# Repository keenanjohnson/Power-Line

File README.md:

###Current design###
4 "devices", communication is from top to bottom and vice versa:

* Arduino + Ethernet Shield -> (Ethernet cable) -> Router
* Router -> (Ethernet cable) -> PLN 1
* PLN 1 -> power line -> PLN 2
* PLN 2 -> (Ethernet cable) -> Arduino + Ethernet Sheild

####Information####
Ensure that the node devices all have different MAC addresses to get different IP addresses from the host router. The router should be set up to deliver a certain IP address to the MAC address of the base station. In our project's current state, it is meant to be delivered 192.168.2.50 but will setup its own IP address if that one is unobtainable. The nodes will just listen for the IP address so this is mainly important for access the website, which you will require you to know the IP address.

###Powerline###

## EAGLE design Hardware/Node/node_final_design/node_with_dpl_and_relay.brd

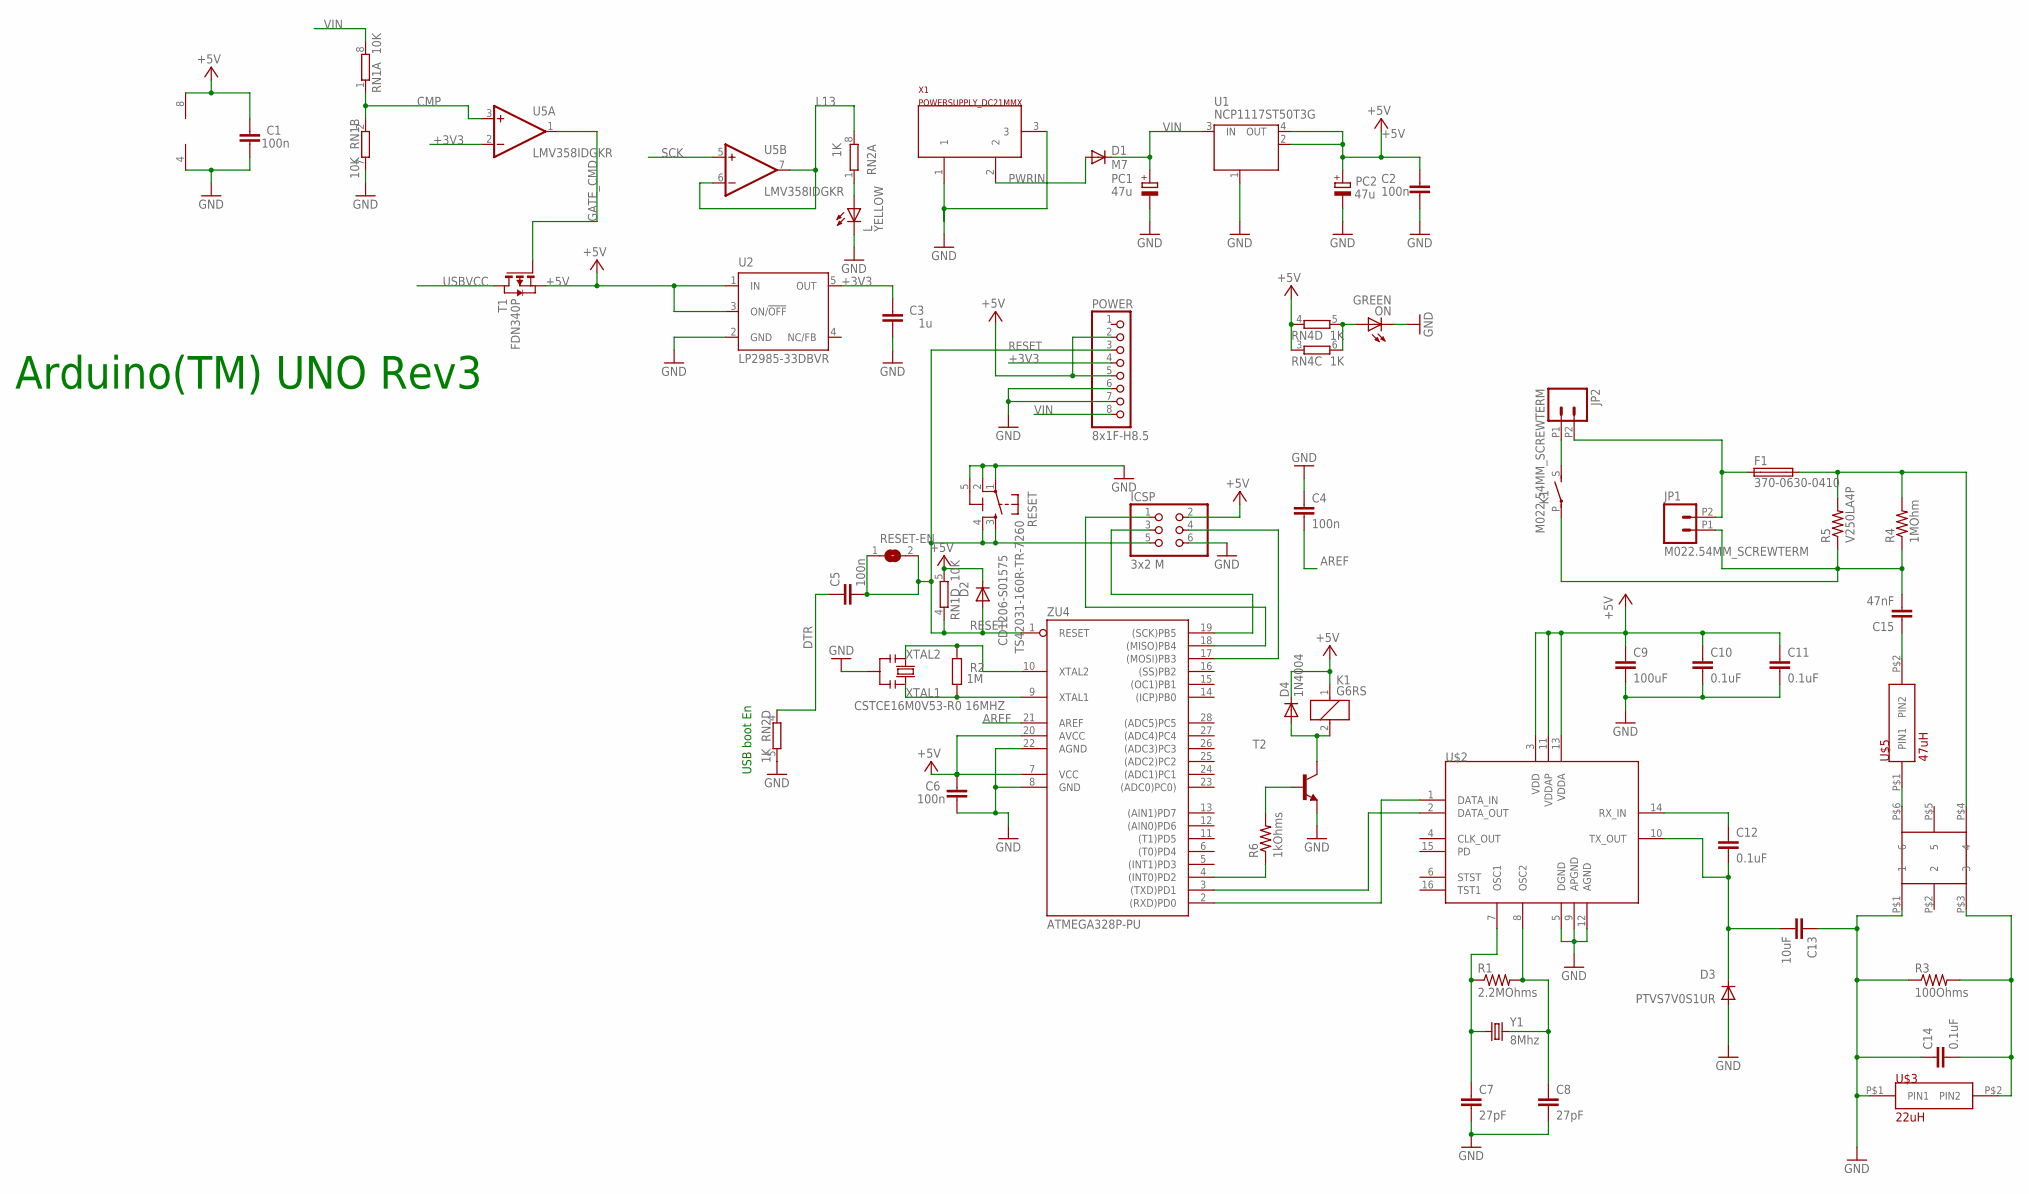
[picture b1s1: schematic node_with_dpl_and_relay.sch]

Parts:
C1, C2, C4, C5, C6: 100n; C0603-ROUND
C3: 1u; C0603-ROUND
C7, C8: 27pF; 1206
C9: 100uF; 1206
C10, C11, C14: 0.1uF; 1206
C12: 0.1uF; AXIAL-5MM
C13: 10uF; CAP-PTH-SMALL
C15: 47nF; C15B5
D1: M7; SMB
D2: CD1206-S01575; MINIMELF
D3: PTVS7V0S1UR; SOD-123_MINI-SMA
D4: 1N4004; DO41-10
F1: 370-0630-0410; TR5
ICSP: 3x2 M; 2X03
JP1, JP2: M022.54MM_SCREWTERM; 1X02_2.54_SCREWTERM
K1: G6RS
L: YELLOW; CHIP-LED0805
ON: GREEN; CHIP-LED0805
PC1, PC2: 47u; PANASONIC_D
POWER: 8x1F-H8.5; 1X08
R1: 2.2MOhms; 1206
R2: 1M; R0603-ROUND
R3: 100Ohms; AXIAL-0.5
R4: 1MOhm; AXIAL-0.3-KIT
R5: V250LA4P; AXIAL-0.4
R6: 1kOhms; 0204V
RESET: TS42031-160R-TR-7260; TS42
RESET-EN: SJ
RN1: 10K; CAY16
RN2, RN4: 1K; CAY16
T1: FDN340P; SOT-23
T2: 2N5401-NPN-TO92-CBE; TO92-CBE
U1: NCP1117ST50T3G; SOT223
U2: LP2985-33DBVR; SOT23-DBV
U5: LMV358IDGKR; MSOP08
U$2: TDA5052AT; SO16L
U$3: 22uH; RFB0807-220L
U$4: 78250MC
U$5: 47uH; RFB0807-220L
X1: POWERSUPPLY_DC21MMX; POWERSUPPLY_DC-21MM
Y1: 8Mhz; HC49US
Y2: CSTCE16M0V53-R0 16MHZ; RESONATOR
ZU4: ATMEGA328P-PU; DIL28-3

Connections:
+3V3: C3.2, POWER.4, U2.5 (OUT), U5.2 (-IN)
+5V: C1.2, C2.2, C6.2, C9.1, C10.1, C11.1, D2.C, D4.C, ICSP.2, K1.1, PC2.+, POWER.2, POWER.5, RN1.5 (2), RN4.3 (1), RN4.4 (1), T1.2 (S), U1.2 (OUT), U1.4 (OUT), U2.1 (IN), U2.3 (ON/!OFF), U5.8 (V+), U$2.3 (VDD), U$2.11 (VDDAP), U$2.13 (VDDA), ZU4.7 (VCC), ZU4.20 (AVCC)
AREF: C4.2, ZU4.21 (AREF)
CMP: RN1.1, RN1.2 (1), U5.3 (+IN)
DTR: C5.1, RN2.4 (1)
GATE_CMD: T1.3 (G), U5.1 (OUT)
GND: C1.1, C2.1, C3.1, C4.1, C6.1, C7.2, C8.2, C9.2, C10.2, C11.2, C13.1, C14.1, D3.A, ICSP.6, L.C, ON.C, PC1.-, PC2.-, POWER.6, POWER.7, R3.P$1 (1), RESET.1, RESET.2, RESET.5 (5-GND), RN1.7 (2), RN2.5 (2), T2.E, U1.1 (GND/ADJ), U2.2 (GND), U5.4 (V-), U$2.5 (DGND), U$2.9 (APGND), U$2.12 (AGND), U$3.P$1 (PIN1), U$4.P$1 (1), X1.1, X1.3, Y2.2, ZU4.8 (GND), ZU4.22 (AGND)
L13: RN2.8 (2), U5.6 (-IN), U5.7 (OUT)
MISO: ICSP.1, ZU4.18 ((MISO)PB4)
MOSI: ICSP.4, ZU4.17 ((MOSI)PB3)
unnamed: L.A, RN2.1
unnamed: C8.1, R1.2, U$2.8 (OSC2), Y1.2
unnamed: ON.A, RN4.5 (2), RN4.6 (2)
unnamed: C7.1, R1.1, U$2.7 (OSC1), Y1.1
unnamed: C12.P$1 (1), U$2.14 (RX_IN)
unnamed: C12.P$2 (2), C13.2, D3.C, U$2.10 (TX_OUT)
unnamed: C14.2, R3.P$2 (2), U$3.P$2 (PIN2), U$4.P$3 (3)
unnamed: U$4.P$6 (6), U$5.P$1 (PIN1)
unnamed: C15.1, U$5.P$2 (PIN2)
unnamed: F1.2, R4.P$2 (2), R5.P$2 (2), U$4.P$4 (4)
unnamed: JP2.P1 (1), K1.S
unnamed: F1.1, JP1.P2 (2), JP2.P2 (2)
unnamed: U$2.2 (DATA_OUT), ZU4.3 ((TXD)PD1)
unnamed: U$2.1 (DATA_IN), ZU4.2 ((RXD)PD0)
unnamed: R6.1, ZU4.4 ((INT0)PD2)
unnamed: R6.2, T2.B
unnamed: D4.A, K1.2, T2.C
unnamed: C15.2, JP1.P1 (1), K1.P, R4.P$1 (1), R5.P$1 (1)
PWRIN: D1.A, X1.2
RESET: C5.2, D2.A, ICSP.5, POWER.3, RESET.3, RESET.4, RESET-EN.1, RESET-EN.2, RN1.4 (1), ZU4.1 (RESET)
SCK: ICSP.3, U5.5 (+IN), ZU4.19 ((SCK)PB5)
USBVCC: T1.1 (D)
VIN: D1.C, PC1.+, POWER.8, RN1.8 (2), U1.3 (IN)
XTAL1: R2.1, Y2.3, ZU4.9 (XTAL1)
XTAL2: R2.2, Y2.1, ZU4.10 (XTAL2)

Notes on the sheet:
Arduino(TM) UNO Rev3
USB boot En

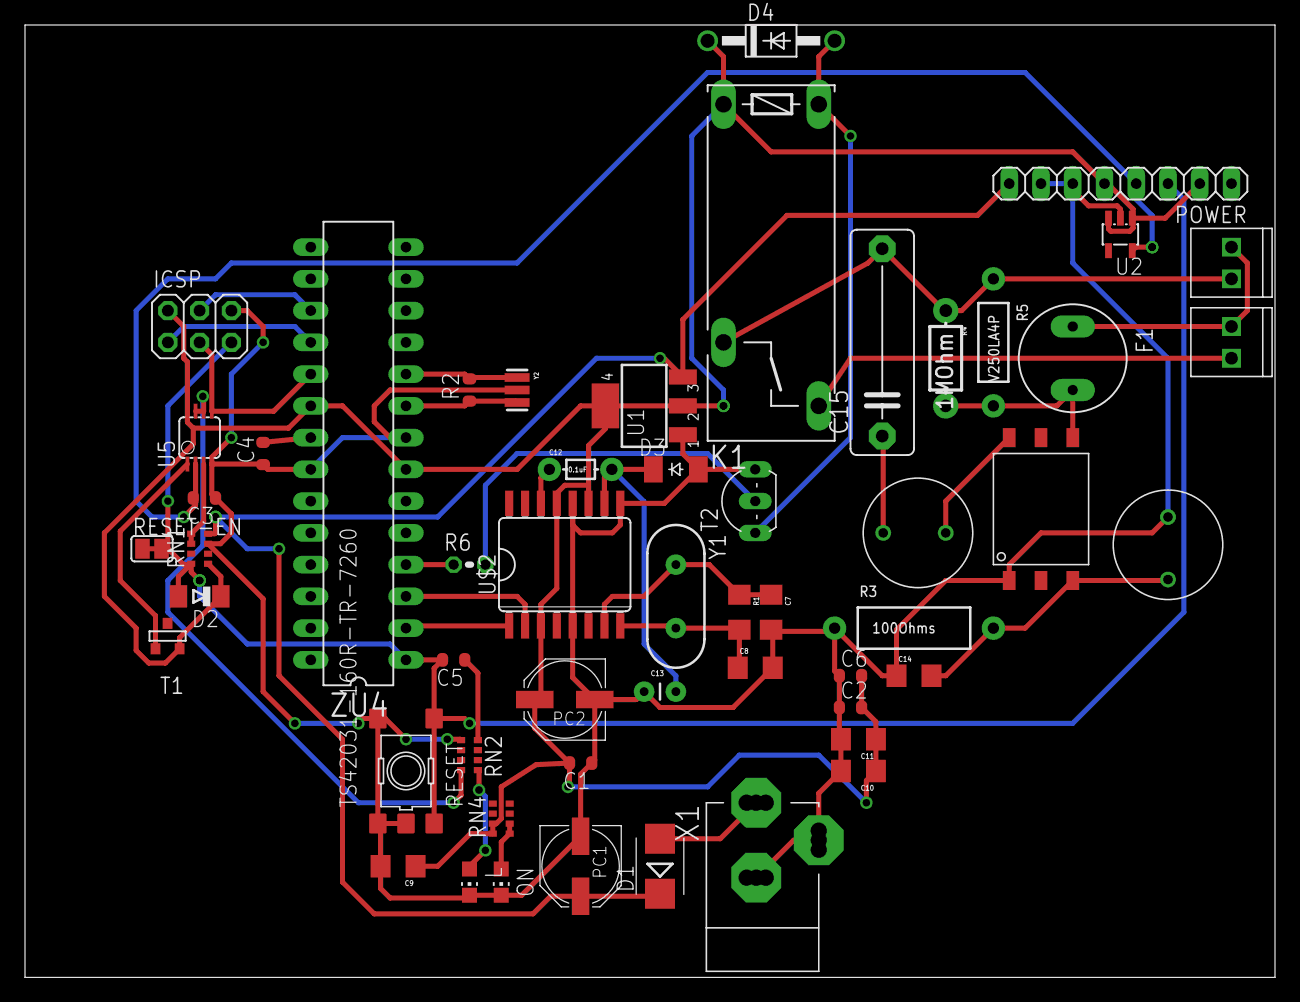
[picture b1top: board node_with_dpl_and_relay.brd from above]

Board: 2 copper layers, 100.0 x 76.2 mm, 53 parts (0 on the bottom side), 34 nets.

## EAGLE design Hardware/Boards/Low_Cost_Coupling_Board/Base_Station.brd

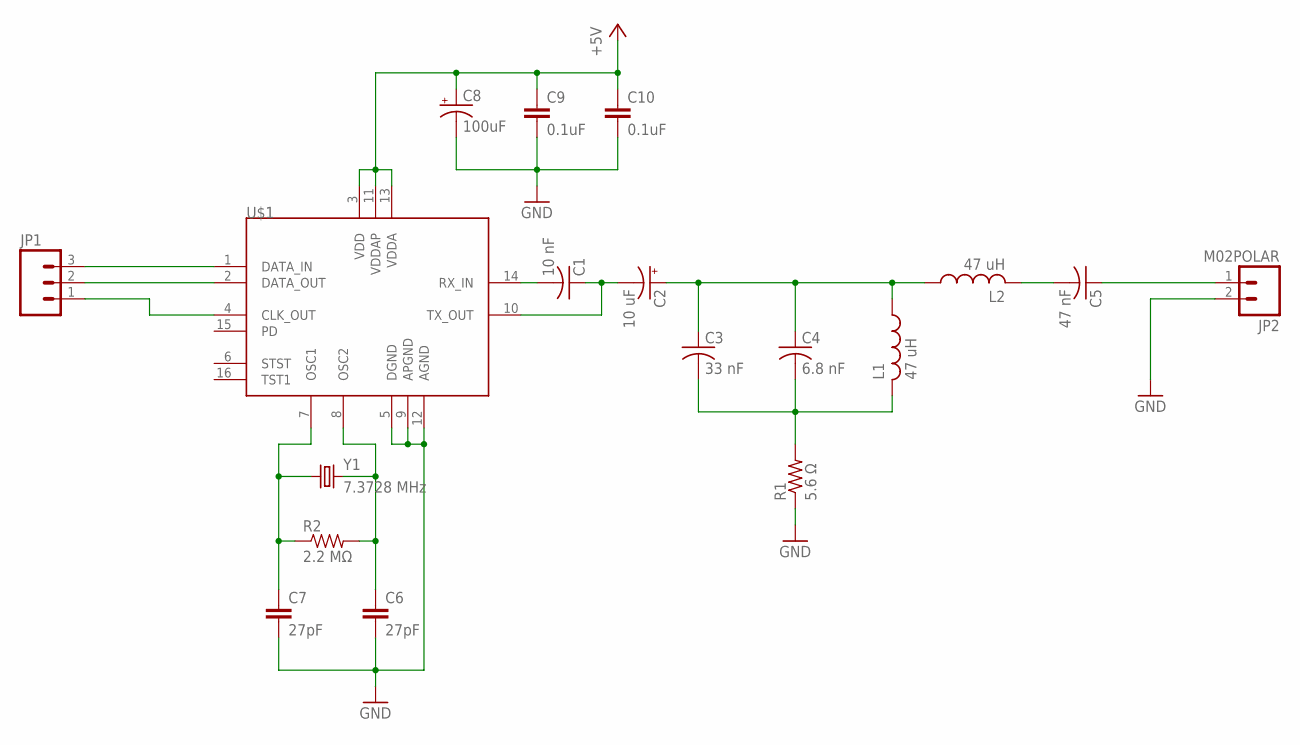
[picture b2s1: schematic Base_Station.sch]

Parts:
C1: 10 nF; C025-030X050
C2: 10 uF; E2-5
C3: 33 nF; C050-050X075
C4: 6.8 nF; C102-043X133
C5: 47 nF; C075-063X106
C6, C7: 27pF; CAP-PTH-5MM
C8: 100uF; CPOL-RADIAL-100UF-25V
C9, C10: 0.1uF; CAP-PTH-5MM
JP1: M03POLAR; MOLEX-1X3
JP2: M02POLAR; MOLEX-1X2
L1: 47 uH; 0204/7
L2: 47 uH; 0207/10
R1: 5.6 Ω; 0207/7
R2: 2.2 MΩ; AXIAL-0.4
U$1: TDA5052AT; SO16L
Y1: 7.3728 MHz; HC49US

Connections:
+5V: C8.1 (+), C9.1, C10.1, U$1.3 (VDD), U$1.11 (VDDAP), U$1.13 (VDDA)
GND: C6.2, C7.2, C8.2 (-), C9.2, C10.2, JP2.2, R1.1, U$1.5 (DGND), U$1.9 (APGND), U$1.12 (AGND)
unnamed: C1.2, U$1.14 (RX_IN)
unnamed: C5.2, L2.2
unnamed: C1.1, C2.-, U$1.10 (TX_OUT)
unnamed: C2.+, C3.1, C4.1, L1.1, L2.1
unnamed: C3.2, C4.2, L1.2, R1.2
unnamed: C5.1, JP2.1
unnamed: C7.1, R2.P$1 (1), U$1.7 (OSC1), Y1.1
unnamed: C6.1, R2.P$2 (2), U$1.8 (OSC2), Y1.2
unnamed: JP1.3, U$1.1 (DATA_IN)
unnamed: JP1.2, U$1.2 (DATA_OUT)
unnamed: JP1.1, U$1.4 (CLK_OUT)

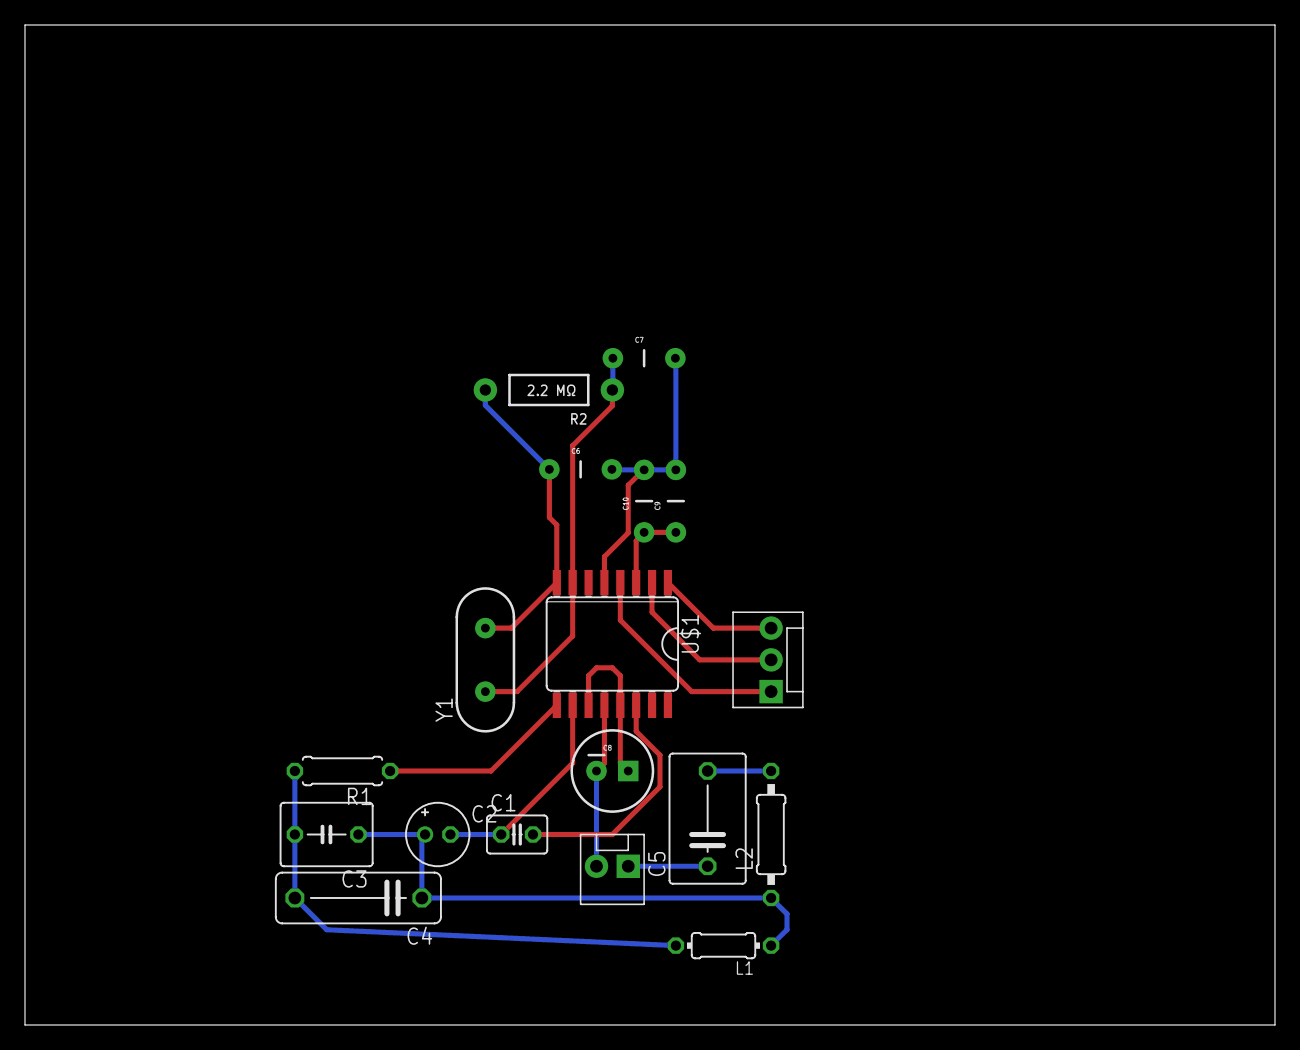
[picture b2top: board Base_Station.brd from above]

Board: 2 copper layers, 100.0 x 80.0 mm, 18 parts (0 on the bottom side), 13 nets.

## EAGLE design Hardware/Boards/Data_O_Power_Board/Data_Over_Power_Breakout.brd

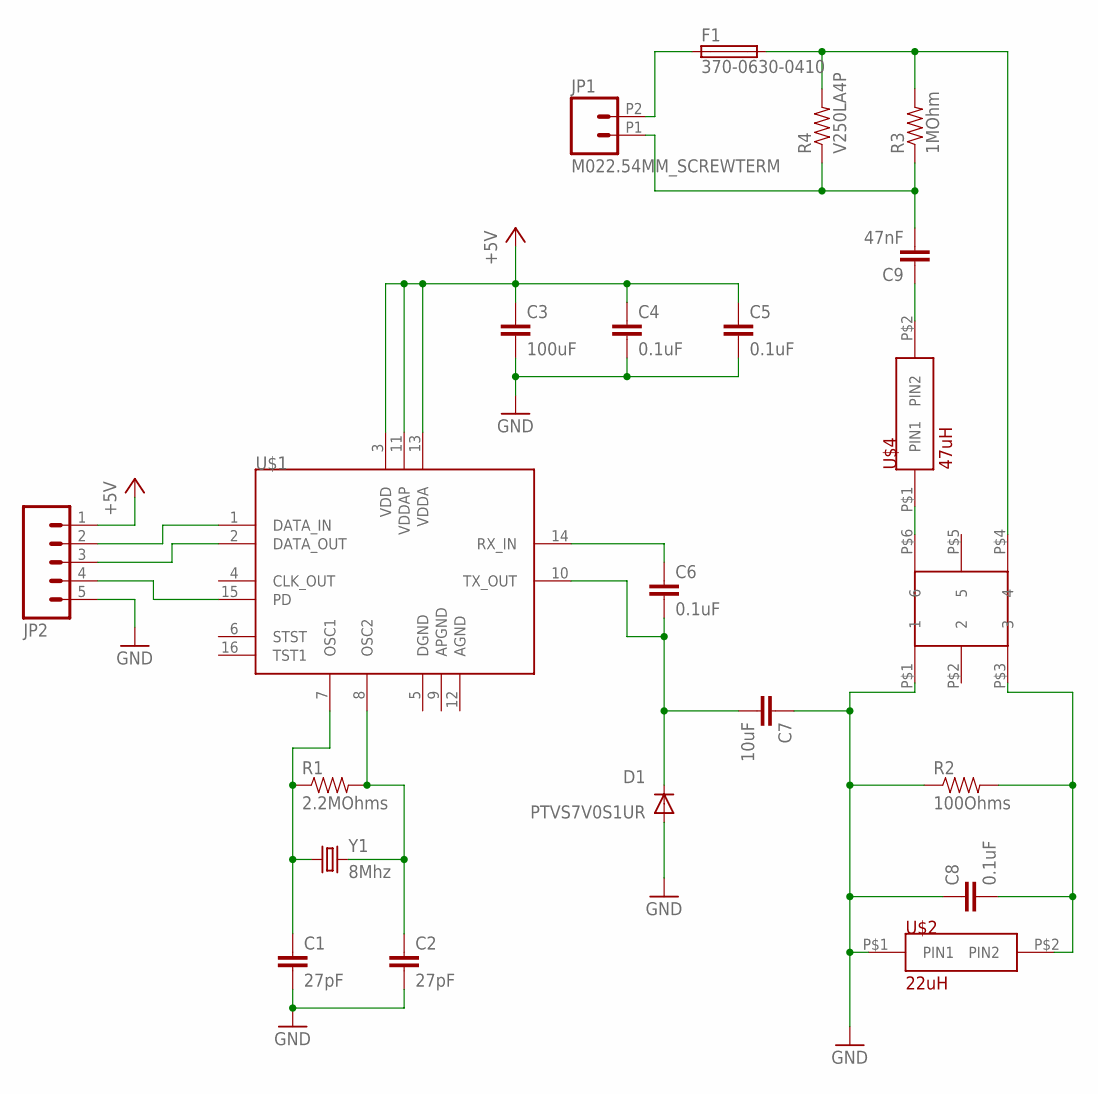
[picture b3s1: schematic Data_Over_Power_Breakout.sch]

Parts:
C1, C2: 27pF; 1206
C3: 100uF; 1206
C4, C5, C8: 0.1uF; 1206
C6: 0.1uF; AXIAL-5MM
C7: 10uF; CAP-PTH-SMALL
C9: 47nF; C15B5
D1: PTVS7V0S1UR; SOD-123_MINI-SMA
F1: 370-0630-0410; TR5
JP1: M022.54MM_SCREWTERM; 1X02_2.54_SCREWTERM
JP2: M05PTH_LONGPADS; 1X05_LONGPADS
R1: 2.2MOhms; 1206
R2: 100Ohms; AXIAL-0.5
R3: 1MOhm; AXIAL-0.3-KIT
R4: V250LA4P; AXIAL-0.4
U$1: TDA5052AT; SO16L
U$2: 22uH; RFB0807-220L
U$3: 78250MC
U$4: 47uH; RFB0807-220L
Y1: 8Mhz; HC49US

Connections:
+5V: C3.1, C4.1, C5.1, JP2.1, U$1.3 (VDD), U$1.11 (VDDAP), U$1.13 (VDDA)
GND: C1.2, C2.2, C3.2, C4.2, C5.2, C7.1, C8.1, D1.A, JP2.5, R2.P$1 (1), U$2.P$1 (PIN1), U$3.P$1 (1)
unnamed: C2.1, R1.2, U$1.8 (OSC2), Y1.2
unnamed: C1.1, R1.1, U$1.7 (OSC1), Y1.1
unnamed: U$3.P$6 (6), U$4.P$1 (PIN1)
unnamed: C8.2, R2.P$2 (2), U$2.P$2 (PIN2), U$3.P$3 (3)
unnamed: C6.P$1 (1), U$1.14 (RX_IN)
unnamed: C6.P$2 (2), C7.2, D1.C, U$1.10 (TX_OUT)
unnamed: C9.1, U$4.P$2 (PIN2)
unnamed: C9.2, JP1.P1 (1), R3.P$1 (1), R4.P$1 (1)
unnamed: F1.2, R3.P$2 (2), R4.P$2 (2), U$3.P$4 (4)
unnamed: F1.1, JP1.P2 (2)
unnamed: JP2.2, U$1.1 (DATA_IN)
unnamed: JP2.3, U$1.2 (DATA_OUT)
unnamed: JP2.4, U$1.15 (PD)

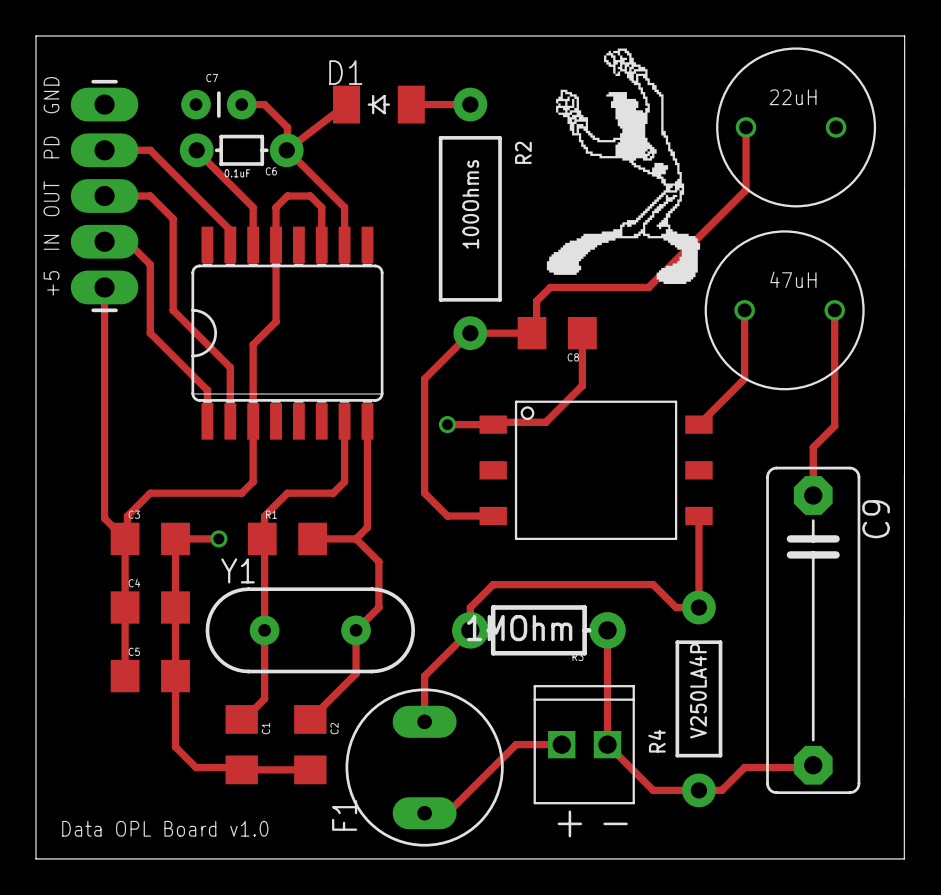
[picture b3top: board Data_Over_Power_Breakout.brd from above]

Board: 2 copper layers, 48.3 x 45.7 mm, 22 parts (0 on the bottom side), 15 nets.

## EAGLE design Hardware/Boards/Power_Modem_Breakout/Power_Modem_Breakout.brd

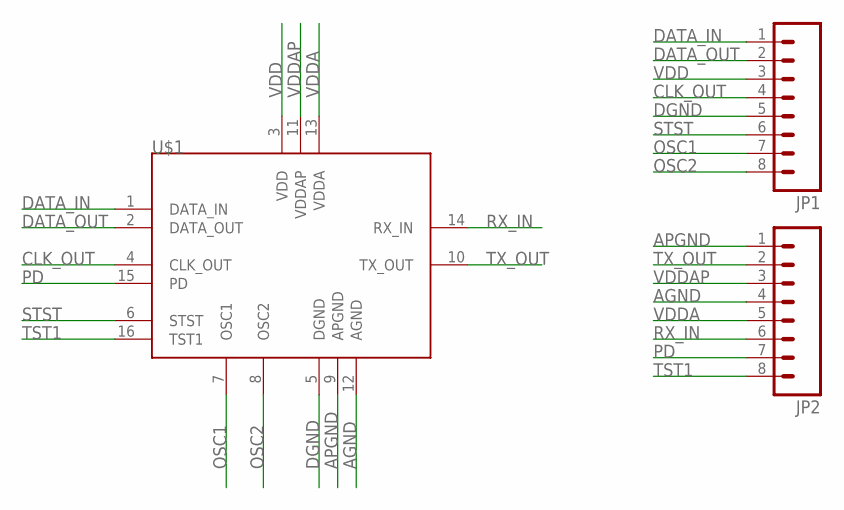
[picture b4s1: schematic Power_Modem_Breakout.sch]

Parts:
JP1, JP2: M08LONGPADS; 1X08_LONGPADS
U$1: TDA5052AT; SO16L

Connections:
AGND: JP2.4, U$1.12 (AGND)
APGND: JP2.1, U$1.9 (APGND)
CLK_OUT: JP1.4, U$1.4 (CLK_OUT)
DATA_IN: JP1.1, U$1.1 (DATA_IN)
DATA_OUT: JP1.2, U$1.2 (DATA_OUT)
DGND: JP1.5, U$1.5 (DGND)
OSC1: JP1.7, U$1.7 (OSC1)
OSC2: JP1.8, U$1.8 (OSC2)
PD: JP2.7, U$1.15 (PD)
RX_IN: JP2.6, U$1.14 (RX_IN)
STST: JP1.6, U$1.6 (STST)
TST1: JP2.8, U$1.16 (TST1)
TX_OUT: JP2.2, U$1.10 (TX_OUT)
VDD: JP1.3, U$1.3 (VDD)
VDDA: JP2.5, U$1.13 (VDDA)
VDDAP: JP2.3, U$1.11 (VDDAP)

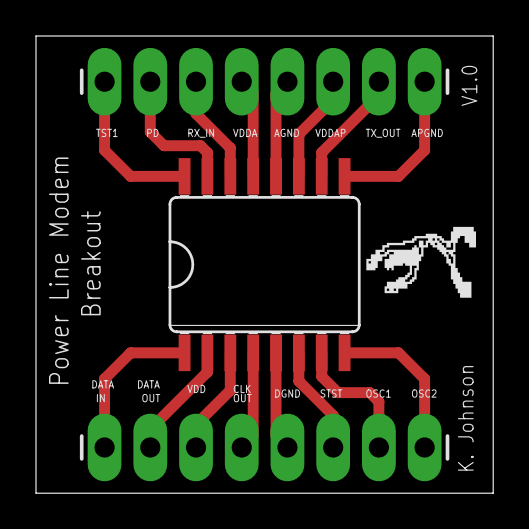
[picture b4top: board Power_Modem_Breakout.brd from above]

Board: 2 copper layers, 25.4 x 25.4 mm, 3 parts (0 on the bottom side), 16 nets.

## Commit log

2014-01-18 Adding power modem datasheet
2014-01-18 Adding Eagle Library for Power Modem
2014-01-18 Created simple breakout for power modem
2014-01-18 Added silkscreen layer
2014-01-18 Adding OSH Park DRC file
2014-01-18 Added really important things to breakout
2014-01-18 Fixed PL so it renders correctly
2014-01-18 Fixed my name
2014-01-18 Removed this file. I don't know why
2014-01-21 Adding image
2014-01-23 Fixed my name layer.
2014-01-29 Adding schematic for power line breakout
2014-01-29 Added DOP Board
2014-02-20 Commiting the test code
2014-02-23 adding application notes
2014-02-23 Updated code from testing
2014-02-24 Add test code to use one Uno + 2 PLN boards
2014-02-25 Working serial between two PLNs
2014-02-25 Update .gitignore to ignore .DS_Store files
2014-02-25 Not sure what changed
2014-03-02 Add webserver code and webpage
    This code will communicate with the webpage via an XML response.
    The status reflected is of the pin 7 and 8 button being emulated
    by a wire connected to GND (off) or 3.3V (on). The code contains
    the first pass at adding elements on the fly commented out.
2014-03-02 Add ability to construct HTML elements in real time
    Constructs the HTML elements representing the lights on the fly
    by appending new elements to the single one on the page based
    upon the XML response.
2014-03-04 Adding webduino stuff
2014-03-04 Introduce packet-level protocol draft
2014-03-18 Update one Uno code to signal LED
2014-03-18 Really dumb code that works
2014-03-24 Adding schematic for long term hardware design
2014-03-25 Added Schematic for low cost coupling board
    Hopefully I didn't mess it up too badly
2014-03-26 Finished schematic for low cost coupling board.
2014-03-27 Adding test code for Matt
2014-03-27 Partially completed low cost coupling board
    Decided it wasn't necessary tonight
2014-04-02 Move WebServer.h to proper folder
2014-04-10 Add initial code for basestation and node
    The Code folder now contains the code for both Arduinos doing
    communication through the powerline. The layout of the components
    is detailed in the header of the files. This should enable
    dynamic connection to the server via grabbing a UDP broadcast
    of the basestation's IP address. The basestation will see the
    client and send commands through the PLN device. The node device
2014-04-10 Move old code to Testing folder and update README
2014-04-10 Fix and update README
2014-04-10 Reset connection to server on disconnect
    If TCP connection to server has gone down, look for UDP broadcast
    and reconnect to new server IP.
    Issue: #10
2014-04-10 Fix send_cmd_to_client function
    Update function to send data to the individual client passed into
    the function instead of to all connected clients.
2014-04-10 Update receiving algorithm on client side
    We can assume the data will be received correctly because of using
    the TCP connection to exchange the data.
2014-04-10 Add dynamic node addition/removal
    client.connected() never seems to disconnect on the server side.
    Use both client.connected() and whether the server can write to
    the client to determine the status of the TCP connection. Server
    will determine that client has been dropped and begin searching
    for a new clients again.
    Issue: #2
2014-04-12 Removing old webduino
2014-04-12 Bring in Webduino submodule
    After this commit you'll need to run 'git submodule update --init'
    to bring in the Webduino submodule.
2014-04-12 Add on/off response to commands
    Initialize relay pin (5) as output and set the value upon receipt of
    the NODE_OFF or NODE_ON commands.
    Issue: #4
2014-04-12 Adding Wedduino file
2014-04-12 Removing old example
2014-04-14 #1 Added basic hello world webduino routing
2014-04-14 Add some uncommitted changes to documentation
2014-04-15 Non working webserver base station with SD card read
2014-04-15 Move strings to progmem
    Move const arrays to progmem to save some RAM space. Remove unused
    globally declared objects. Add start of NODE_STATUS command, still
    need to add implementation.
2014-04-15 Removing old webserver stuff
2014-04-16 Web server is close ish to working
2014-04-16 Hello World with integrated Webduino
2014-04-16 Webduino now serves HTML page from SD card
2014-04-16 Adding index file from Matt's old code as base
2014-04-16 Adding working webserver stuff
2014-04-16 Add status command and server command parsing
    Node can now return status to server. Server can now parse commands
    /respones sent back from node devices.
    Issue: #13
2014-04-16 Add node on/off functionality with status update
    Issue: #6
2014-04-18 Send NODE_STATUS to server after NODE_ON/OFF
    Process NODE_ON/OFF and send NODE_STATUS to server to update its
    state for the selected node.
    Issue: #16
2014-04-18 Add node disconnecting from base logic
    The nodes can now detect that the base has been disconnected and
    they will starting searching for new base. They rely on a cmd
    sent to server (NODE_KEEP_ALIVE) receiving a reply back under the
    time limit (2000 loops). Every NODE_KEEP_ALIVE sent from server
    contains the status of the relay pin, so use this to update the
    node_status on the server side. This will cause less traffic than
2014-04-18 Add server disconnecting from node logic
    Server will disconnect from node if it hasn't seen a NODE_KEEP_ALIVE
    in (2 * LOOP_COUNT_RESET). It will then return to the accepting
    connections state. The current timeout is loop cycle based but
    it would be better to do it time based.
    Issue: #15
2014-04-18 Start multinode support
    Setup arrays for node status/timeout and for individual Ethernet
    Client storage per connected node. Limit connections by max sockets
    available to Ethernet Shield. Most accesses are hard coded due to
    the server only giving out the 0x01 ID to all connected nodes.
    Looping over the arrays needs to be added to finish this setup.
    Issue: #7
2014-04-21 #14 Webpage now dynamically generates buttons for lights. Light state is also represented by button color. Commanding is broken for now
2014-04-21 #14 Device buttons now generate unique post messages
2014-04-22 Change node/server timeout to time based
    Nodes now disconnect from server if a KEEP_ALIVE isn't received
    within 0.5 seconds from sending one. Server now disconnects if a
    KEEP_ALIVE isn't recieved from a node within 1 second.
    Add looping over multiple nodes. This needs to be tested before it
    can be verified.
    Issue: #18
2014-04-22 Complete multi-node processing
    Multiple nodes can now connect. Nodes will timeout individually
    based on the previous timeout values. A new ID will be given to a
    new connection that hasn't been established before. All Serial.
    print/println strings have now been moved to PROGMEM to save RAM.
    IMPORTANT:
    To get this patch to work, you must copy the files in
2014-04-22 Updated webpage post request
2014-04-30 docs update
2014-04-30 Add dynamic node count HTTP response
    Uses the connceted_node_count to return the amount of nodes to the
    HTTP requests. Improve algorithm for sending NODE_ON/NODE_OFF to
    the individual nodes by ID returned from the server.
2014-04-30 Fixed website title and update rate
2014-04-30 Close UDP socket when MAX conns reached
    Close UDP socket to open up more sockets for other nodes and/or
    webserver traffic.
2014-04-30 Clean up spaces on empty lines
2014-04-30 Update MAC and pin for demo presentation
2014-04-30 Add physical housing files
    Add physical housing files created in Autodesk Inventor. Contains
    the individual drawing files as well as an assembly file with the
    two parts placed together. The .stl files were generated to send
    to the 3D printer and are included.
2014-04-30 Update ReadMe with new information
2014-04-30 Change units of .stl files to inches
2014-05-04 Fix website update upon node dropout
    Website can now respond to dropping out a light that happens to be
    under than maximum index. For example, light1 when there are two
    lights connect. It will search through the XML response until it
    finds the amount of expected lights.
2014-05-04 Buttons are now bigger
2014-05-04 Schematic for nodes
    Includes dpl circuit, relay, and arduino itself
2014-05-04 improve web page styling
2014-05-04 oops, don't add dummy buttons
2014-05-04 update title of device control center
2014-05-04 Removing -'s
2014-05-05 Started node pcb layout
    not finished yet
2014-05-13 node pcb done
    should work

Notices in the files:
parts and their libraries:
SparkFun-Passives: Licensing: CC v3.0 Share-Alike You are welcome to use this library for commercial purposes.
